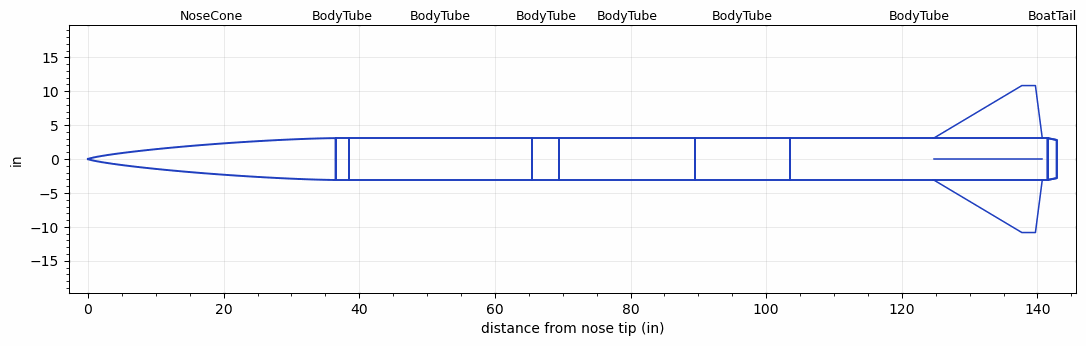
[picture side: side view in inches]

<RASAeroDocument>
 <FileVersion>2</FileVersion>
 <RocketDesign>
  <NoseCone>
   <Length>36.4999</Length>
   <Diameter>6.17</Diameter>
   <Shape>Von Karman Ogive</Shape>
   <Location>0</Location>
  </NoseCone>
  <BodyTube>
   <Length>2</Length>
   <Diameter>6.17</Diameter>
   <Location>36.4999</Location>
  </BodyTube>
  <BodyTube>
   <Length>26.9999</Length>
   <Diameter>6.17</Diameter>
   <Location>38.4999</Location>
  </BodyTube>
  <BodyTube>
   <Length>4</Length>
   <Diameter>6.17</Diameter>
   <Location>65.4998</Location>
  </BodyTube>
  <BodyTube>
   <Length>20</Length>
   <Diameter>6.17</Diameter>
   <Location>69.4998</Location>
  </BodyTube>
  <BodyTube>
   <Length>14</Length>
   <Diameter>6.17</Diameter>
   <Location>89.4998</Location>
  </BodyTube>
  <BodyTube>
   <Length>37.9999</Length>
   <Diameter>6.17</Diameter>
   <RailGuideDiameter>0.621</RailGuideDiameter>
   <RailGuideHeight>0.6845</RailGuideHeight>
   <Location>103.4998</Location>
   <BoattailLength>1.353</BoattailLength>
   <BoattailRearDiameter>5.62</BoattailRearDiameter>
   <Fin>
    <Count>4</Count>
    <Chord>16</Chord>
    <Span>7.75</Span>
    <SweepDistance>12.9904</SweepDistance>
    <TipChord>2</TipChord>
    <Thickness>0.3125</Thickness>
    <LERadius>0.05</LERadius>
    <Location>16.7874</Location>
    <AirfoilSection>Hexagonal</AirfoilSection>
    <FX1>1</FX1>
    <FX3>0.5</FX3>
   </Fin>
  </BodyTube>
  <BoatTail>
   <Length>1.353</Length>
   <Diameter>6.17</Diameter>
   <RearDiameter>5.62</RearDiameter>
   <Location>141.4997</Location>
  </BoatTail>
  <Surface>Camouflage Paint</Surface>
  <ModifiedBarrowman>True</ModifiedBarrowman>
  <Turbulence>True</Turbulence>
  <UseBooster1>False</UseBooster1>
  <UseBooster2>False</UseBooster2>
 </RocketDesign>
 <LaunchSite>
  <Altitude>3000</Altitude>
  <Pressure>29.92</Pressure>
  <RodAngle>6</RodAngle>
  <RodLength>17</RodLength>
  <Temperature>100</Temperature>
  <WindSpeed>0</WindSpeed>
 </LaunchSite>
 <Recovery>
  <Altitude1>1000</Altitude1>
  <Altitude2>656.168</Altitude2>
  <DeviceType1>Parachute</DeviceType1>
  <DeviceType2>Parachute</DeviceType2>
  <Event1>True</Event1>
  <Event2>True</Event2>
  <Size1>119.9998</Size1>
  <Size2>24</Size2>
  <EventType1>Altitude</EventType1>
  <EventType2>Apogee</EventType2>
  <CD1>1.16</CD1>
  <CD2>0</CD2>
 </Recovery>
 <SimulationList>
  <Simulation>
   <SustainerEngine>O3380  (TRT)</SustainerEngine>
   <SustainerLaunchWt>120</SustainerLaunchWt>
   <SustainerNozzleDiameter>3.4</SustainerNozzleDiameter>
   <SustainerCG>103.2</SustainerCG>
   <SustainerIgnitionDelay>0</SustainerIgnitionDelay>
   <Booster1SeparationDelay>0</Booster1SeparationDelay>
   <Booster1IgnitionDelay>0</Booster1IgnitionDelay>
   <IncludeBooster1>False</IncludeBooster1>
   <Booster2Delay>0</Booster2Delay>
   <IncludeBooster2>False</IncludeBooster2>
   <TimetoApogee>43.45871</TimetoApogee>
   <MaxAltitude>30947.59</MaxAltitude>
   <MaxVelocity>1769.401</MaxVelocity>
  </Simulation>
  <Simulation>
   <SustainerLaunchWt>119.6303</SustainerLaunchWt>
   <SustainerCG>103.2035</SustainerCG>
   <SustainerIgnitionDelay>0</SustainerIgnitionDelay>
   <Booster1SeparationDelay>0</Booster1SeparationDelay>
   <Booster1IgnitionDelay>0</Booster1IgnitionDelay>
   <IncludeBooster1>False</IncludeBooster1>
   <Booster2Delay>0</Booster2Delay>
   <IncludeBooster2>False</IncludeBooster2>
  </Simulation>
  <Simulation>
   <SustainerLaunchWt>46.8303</SustainerLaunchWt>
   <SustainerCG>77.6254</SustainerCG>
   <SustainerIgnitionDelay>0</SustainerIgnitionDelay>
   <Booster1SeparationDelay>0</Booster1SeparationDelay>
   <Booster1IgnitionDelay>0</Booster1IgnitionDelay>
   <IncludeBooster1>False</IncludeBooster1>
   <Booster2Delay>0</Booster2Delay>
   <IncludeBooster2>False</IncludeBooster2>
  </Simulation>
  <Simulation>
   <SustainerLaunchWt>114.2845</SustainerLaunchWt>
   <SustainerCG>99.6849</SustainerCG>
   <SustainerIgnitionDelay>0</SustainerIgnitionDelay>
   <Booster1SeparationDelay>0</Booster1SeparationDelay>
   <Booster1IgnitionDelay>0</Booster1IgnitionDelay>
   <IncludeBooster1>False</IncludeBooster1>
   <Booster2Delay>0</Booster2Delay>
   <IncludeBooster2>False</IncludeBooster2>
  </Simulation>
 </SimulationList>
</RASAeroDocument>
